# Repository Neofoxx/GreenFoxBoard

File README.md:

# GreenFoxBoard
This is a small PIC32MM GPM development board.

#### Schematic

#### Render

#### PCB

## Description
This is a small PIC32MM dev board, for the GPM series of parts (aka /w USB support).

The idea is to have a board, that can be quickly used with the [open-source toolchain for PIC32s](https://gitlab.com/spicastack/pic32-parts-free).

The feature list is as follows:
- PIC32MM0256GPM036-I/M2, 2.0V to 3.6V, 25MHz max., 256kB flash, 32kB RAM
- USB-C connector
- ESD protection on USB pins
- Two LEDs, one Power, one User
- Two buttons, one Reset, one User
- Components only on one side
- Fits into 28-pin DIP socket (wide)
- Breakaway section on the PCB, with a JTAG+UART connector for easy programming
- Pin markings on both top and bottom

The JTAG+UART connector is there for ease of access. You can also score the vias with a knife, and break that part off. The JTAG+UART pins are also available on other pins, not just on the breakaway.

ICSP pins are routed to the bottom left of the board, in a standard ICD/PICkit pinout, for easy connecting.

Two crystals are present - an 8MHz one and a 32.768kHz one. Pins used for these crystals are not routed to the header pins.

USB works without any crystals - USB clock tuning on-the-go built into the peripheral is confirmed working. Tested with a modified version of [m-stack](https://github.com/signal11/m-stack).

## Notes

Be careful when ordering the chips, as theee are two 36-pin namings, but one actually has 40-pins. You needs the PIC32MM0256GPM036-I/**M2** version, **not MV**

Make sure to use the latest fersion of [Progyon](https://gitlab.com/spicastack/progyon) for programming, as it includes a fix that previously disabled JTAG pins for use during runtime.

## Files
* The Gerber files are in the HW/GreenFox/Gerbers directory
* The BOM is in the HW/GreenFox/ibom directory
* The schematic is here in the root directory

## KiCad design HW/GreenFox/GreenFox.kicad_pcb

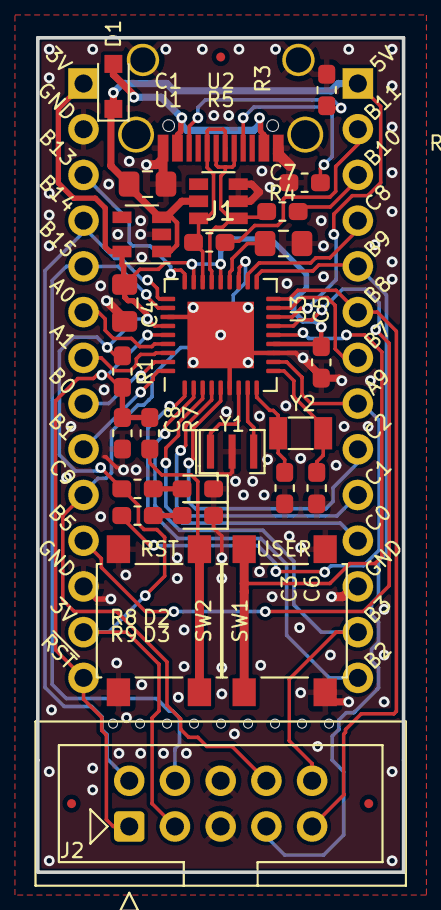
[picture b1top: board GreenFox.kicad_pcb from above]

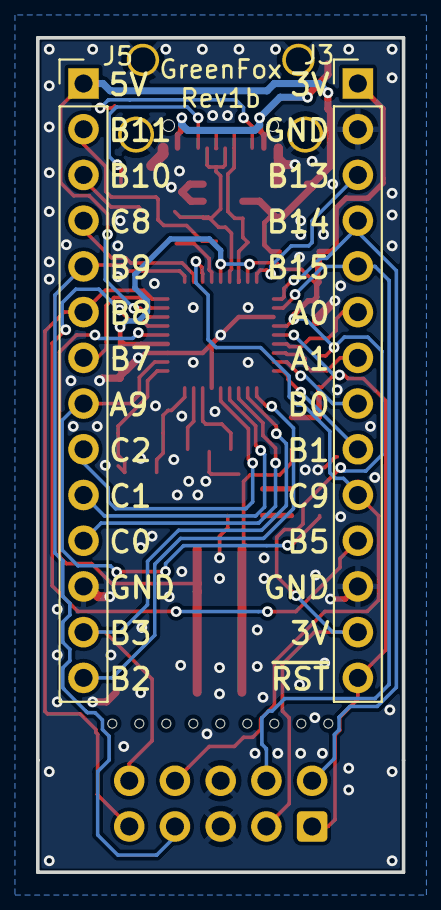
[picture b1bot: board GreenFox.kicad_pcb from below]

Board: 2 copper layers, 20.3 x 46.4 mm, 42 parts (3 on the bottom side), 39 nets.

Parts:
C1, C4: 4.7uF; C_0805_2012Metric_Pad1.15x1.40mm_HandSolder
C3, C6: 27pF; C_0603_1608Metric_Pad1.05x0.95mm_HandSolder
C5, C8: 100nF; C_0603_1608Metric_Pad1.05x0.95mm_HandSolder
C7: 10uF; C_0805_2012Metric_Pad1.15x1.40mm_HandSolder
D1: D_Schottky; D_SOD-323_HandSoldering
D2, D3: LED; LED_0603_1608Metric_Pad1.05x0.95mm_HandSolder
FID1, FID2, FID3: Fiducial; Fiducial_0.5mm_Mask1mm
H1, H2, H3, H4, H5, H6, H7, H8, H9: MB_0.5mm; MouseBiteHole_0.5mm
J1: USB_C_Receptacle_USB2.0; Jing_USB_C_2_0_16pin_receptable_noSlots
J2: Conn_02x05_Odd_Even; IDC-Header_2x05_P2.54mm_Vertical
J3, J5: Conn_01x14; PinHeader_1x14_P2.54mm_Vertical
MARK1: LOGO; FOX_LOGO_MASK
R1, R8, R9: 10k; R_0603_1608Metric_Pad1.05x0.95mm_HandSolder
R2, R3: 5k1; R_0603_1608Metric_Pad1.05x0.95mm_HandSolder
R4, R5: DNS; R_0603_1608Metric_Pad1.05x0.95mm_HandSolder
R7: 100R; R_0603_1608Metric_Pad1.05x0.95mm_HandSolder
SW1, SW2: SW_Push; SW_SPST_B3S-1000
U1: LN1134-3.3V; SOT-23-5
U2: SRV05-4; SOT-23-6
U3: PIC32MM0256GPM036-IM2; QFN-36-1EP_6x6mm_P0.5mm_EP3.7x3.7mm
Y1: 8MHz; Resonator_SMD_muRata_CSTxExxV-3Pin_3.0x1.1mm
Y2: 32.768kHz; Crystal_SMD_3215-2Pin_3.2x1.5mm

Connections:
+3V3: C4.1, C5.1, J2.3, J3.1, J3.13, R1.2, R8.2, U1.5 (VOUT), U3.13 (VDD), U3.23 (VDD), U3.26 (VUSB3V3), U3.31 (AVDD)
+5V: C1.1, D1.1 (K), J5.1, U1.1 (VIN), U1.3 (EN), U2.5 (VP), U3.16 (VBUS/RB6)
/BTN_USER: SW2.1, U3.14 (RC3)
/LED_USER: J5.8, R9.2, U3.11 (RP24/OCM3A/RA9)
/OSC1: U3.7 (OSC1/CLKI/AN5/RP3/OCM1C/RA2), Y1.1
/OSC2: U3.8 (OSC2/CLKO/AN6/C3IND/RP4/OCM1D/RA3), Y1.3
/PGED3: J3.11, U3.15 (PGED3/RP11/ASDA1/USBID/~SS3/FSYNC3/OCM3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)
/RA0\AN0: J3.6, U3.33 (PGEC2/VREF+/CVREF+/AN0/RP1/OCM1E/INT3/R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)
/RA1\AN1: J3.7, U3.34 (PGED2/VREF-/AN1/RP2/OCM1F/RA1)
/RB0\AN2: J3.8, U3.35 (PGED1/AN2/C1IND/C2INB/C3INC/RP6/OCM2C/R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)
/RB1\AN3: J3.9, U3.36 (PGEC1/AN3/C1INC/C2INA/RP7/OCM2D/RB1)
/RB2\AN4: J5.14, U3.1 (AN4/C1INB/RP8/SDA2/OCM2E/RB2)
/RB7: J5.7, U3.17 (RP12/SDA3/SDI3/OCM3F/RB7)
/RB10: J5.3, R4.1
/RB11: J5.2, R5.1
/RB13\AN8: J3.3, U3.27 (AN8/RP15/SCL3/SCK3/RB13)
/RC0\AN12: J5.11, U3.3 (AN12/C2IND/T2CK/T2G/RC0)
/RC1\AN13: J5.10, U3.4 (AN13/T3CK/T3G/RC1)
/RC2: J5.9, U3.5 (RP19/OCM2A/RC2)
/RC8\AN14: J5.4, U3.20 (AN14/LVDIN/C2INC/RC8)
/SOSCI: C3.1, U3.9 (SOSCI/AN7/RP10/OCM3C/RB4), Y2.1
/SOSCO: C6.1, U3.10 (SOSCO/SCLKI/RP5/PWRLCLK/OCM3D/RA4), Y2.2
/TCK: J2.9, J5.6, U3.18 (TCK/RP13/SCL1/~U1CTS/SCK1/OCM1A/RB8)
/TDI: J2.10, J5.13, U3.2 (TDI/AN11/C1INA/RP9/SCL2/OCM2F/RB3)
/TDO\PGEC3: J2.8, J3.10, U3.21 (PGEC3/TDO/RP18/ASCL1/USBOEN/SDO3/RC9)
/TMS: J2.7, J5.5, U3.19 (TMS/REFCLKI/RP14/SDA1/T1CK/T1G/~U1RTS/U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)
/UART1_RX: J2.4, J3.5, U3.29 (AN10/C3INA/REFCLKO/RP17/U1RX/~SS1/FSYNC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)
/UART1_TX: J2.2, J3.4, U3.28 (CVREF/AN9/C3INB/RP16/RTCC/U1TX/VBUSON/S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)
/USBDM: J1.A7 (D-), J1.B7 (D-), R4.2, U2.1 (IO1), U3.24 (D-/RB10)
/USBDP: J1.A6 (D+), J1.B6 (D+), R5.2, U2.6 (IO4), U3.25 (D+/RB11)
/VCAP: C7.1, U3.22 (VCAP)
/~RESET: C8.1, J2.1, J3.14, R1.1, R7.2, U3.32 (~MCLR)
GND: C1.2, C3.2, C4.2, C5.2, C6.2, C7.2, C8.2, D2.1 (K), D3.1 (K), J1.A1 (GND), J1.S1 (SHIELD), J2.5, J2.6, J3.2, J3.12, J5.12, R2.1, R3.1, SW1.2, SW2.2, U1.2 (GND), U2.2 (VN), U2.3 (IO2), U3.6 (VSS), U3.12 (VSS), U3.30 (AVSS), U3.37 (THERMAL_PAD), Y1.2
unnamed: D1.2 (A), J1.A4 (VBUS)
unnamed: D2.2 (A), R8.1
unnamed: D3.2 (A), R9.1
unnamed: J1.A5 (CC1), R2.2
unnamed: J1.B5 (CC2), R3.2
unnamed: R7.1, SW1.1

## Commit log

2021-01-15 First try
2021-01-16 Add .gitignore
2021-01-16 Finished board, added text, fiducials, logos, etc.
2021-01-16 Remove unnecessary files
2021-01-17 Minor tweaks, added gerbers
2021-01-17 Add text to buttons and re-export
2021-03-13 Added documentation & pics
2022-02-16 Very quick mod for different fab
